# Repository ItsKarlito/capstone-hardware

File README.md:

# capstone-hardware

Capstone Software Repo: https://github.com/vincbeaulieu/Capstone_Software

BOM: https://docs.google.com/spreadsheets/d/17WK9bXRUVKC68JrJrpc6w4yRmb0iwnLNZwZWMupnYeM

Raspberry Pi Connection  

Power Supply Circuit:

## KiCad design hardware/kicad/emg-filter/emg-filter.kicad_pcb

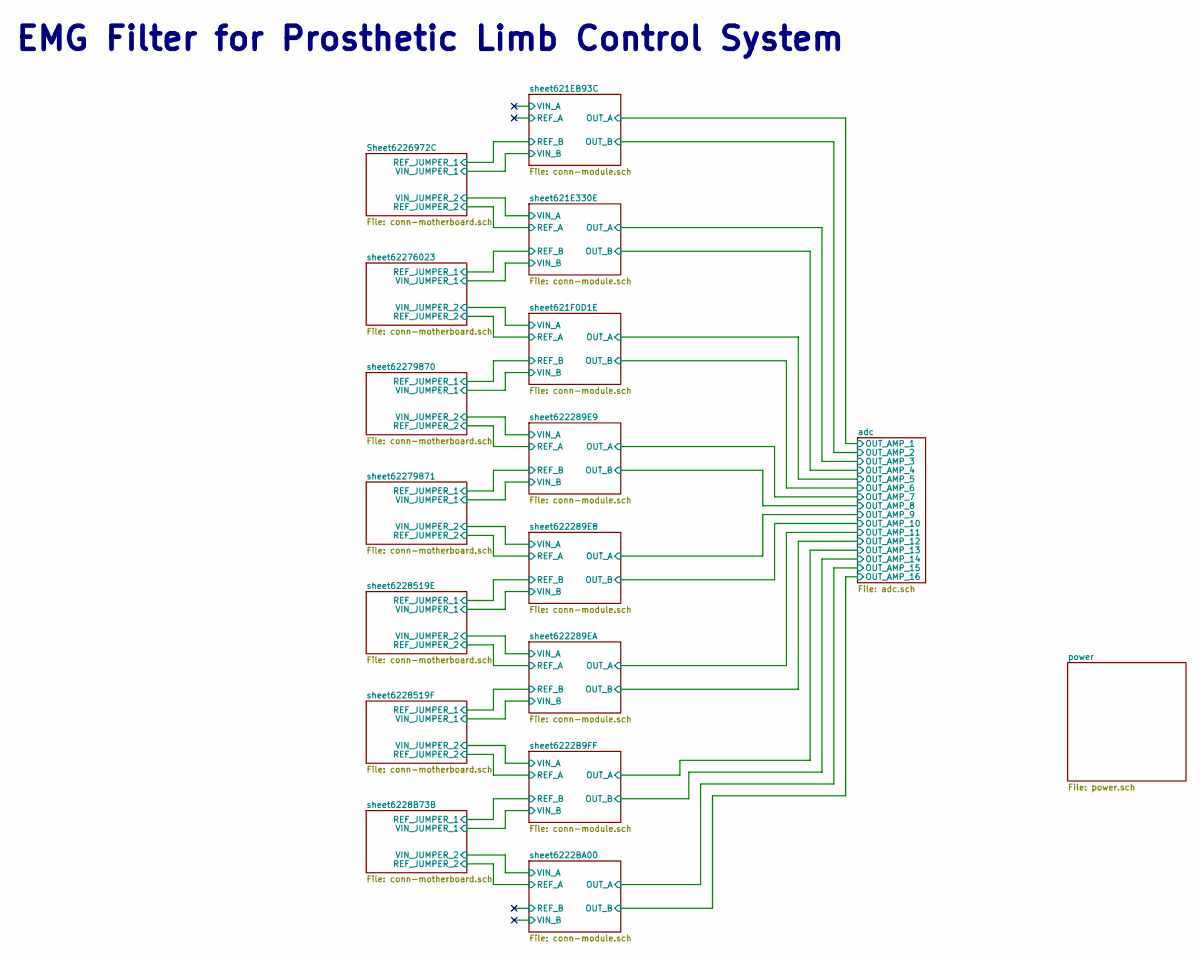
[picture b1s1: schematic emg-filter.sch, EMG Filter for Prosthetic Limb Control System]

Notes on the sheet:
EMG Filter for Prosthetic Limb Control System

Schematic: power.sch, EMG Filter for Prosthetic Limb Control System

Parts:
C1, C9: 1100uF, 50V; CP_Radial_D12.5mm_P5.00mm
C2, C10: 470uF; CP_Elec_10x10
C3, C11: 0.1uF; C_0805_2012Metric
C4, C12: 1uF; C_0805_2012Metric
C5, C13: 0.01uF; C_0805_2012Metric
C6: 0.1uF, 50V; C_0805_2012Metric
C7: 1uF, 50V; C_0805_2012Metric
C8: 0.01uF, 50V; C_0805_2012Metric
D1, D4: 1N4007; D_SOD-123F
D2, D3: LTST-C170TBKT; D_0805_2012Metric
J1: Conn_01x02; EMG_CONN_01x02
J2: Conn_01x03; CONN_01x03
R1, R6: 1k; R_0805_2012Metric
R2, R4: 1M; R_0805_2012Metric
R3, R7: 470; R_0805_2012Metric
R5: 10; R_0805_2012Metric
RV1: 10R_POT; PinHeader_1x03_P2.54mm_Vertical
U1: LM7805_TO220; TO-252-2
U2: LM7905_TO220; TO-263-2

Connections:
+5V: C2.1, C3.1, C4.1, C5.1, D1.2 (A), D2.2, R1.1, U1.3; also elsewhere on the board
+24V: C1.1, C6.1, C7.1, C8.1, D1.1 (K), J1.1, J2.1, R2.1, U1.1
-5V: C10.2, C11.2, C12.2, C13.2, D4.1 (K), R6.2, R7.2, U2.3; also elsewhere on the board
AGND: C1.2, C2.2, C3.2, C4.2, C5.2, C9.1, C10.1, C11.1, C12.1, C13.1, D3.2, J2.2, R2.2, R3.2, R4.1, R5.1, RV1.1, RV1.2; also elsewhere on the board
GNDREF: C6.2, C7.2, C8.2, C9.2, D4.2 (A), J1.2, J2.3, R4.2, U2.2
unnamed: D2.1, R3.1
unnamed: D3.1, R7.1
unnamed: R1.2, RV1.3, U1.2
unnamed: R5.2, R6.1, U2.1

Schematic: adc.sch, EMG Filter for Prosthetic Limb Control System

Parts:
C14, C16, C18, C20: 0.1uF; C_0805_2012Metric
C15, C17, C19, C21: 1.0uF; C_0805_2012Metric
J3: Conn_02x20_Odd_Even; PinHeader_2x20_P2.54mm_Vertical
U3, U4: ADC108S102; TSSOP-16_4.4x5mm_P0.65mm

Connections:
!CS_1_PI: J3.13, U3.1
!CS_2_PI: J3.15, U4.1
+3V3: C16.1, C17.1, C20.1, C21.1, J3.17, U3.13, U4.13
+5V: C14.1, C15.1, C18.1, C19.1, U3.2, U4.2; also elsewhere on the board
/adc/OUT_AMP_2: U3.5; also elsewhere on the board
/adc/OUT_AMP_4: U3.7; also elsewhere on the board
/adc/OUT_AMP_6: U3.9; also elsewhere on the board
/adc/OUT_AMP_8: U3.11; also elsewhere on the board
/adc/OUT_AMP_10: U4.5; also elsewhere on the board
/adc/OUT_AMP_12: U4.7; also elsewhere on the board
/adc/OUT_AMP_14: U4.9; also elsewhere on the board
/adc/OUT_AMP_16: U4.11; also elsewhere on the board
/sheet621E330E/OUT_A: U3.6; also elsewhere on the board
/sheet621EB93C/OUT_A: U3.4; also elsewhere on the board
/sheet621F0D1E/OUT_A: U3.8; also elsewhere on the board
/sheet6222B9FF/OUT_A: U4.8; also elsewhere on the board
/sheet6222BA00/OUT_A: U4.10; also elsewhere on the board
/sheet622289E8/OUT_A: U4.4; also elsewhere on the board
/sheet622289E9/OUT_A: U3.10; also elsewhere on the board
/sheet622289EA/OUT_A: U4.6; also elsewhere on the board
AGND: C14.2, C15.2, C16.2, C17.2, C18.2, C19.2, C20.2, C21.2, J3.25, U3.3, U3.12, U4.3, U4.12; also elsewhere on the board
DIN_MOSI_PI: J3.19, U3.14, U4.14
DOUT_MISO_PI: J3.21, U3.15, U4.15
SCLK_CLK_PI: J3.23, U3.16, U4.16

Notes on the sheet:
TX RX

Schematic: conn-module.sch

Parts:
J4, J6: Conn_01x02; PinSocket_1x02_P2.54mm_Vertical
J5: Conn_01x05; PinSocket_1x05_P2.54mm_Vertical

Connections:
+5V: J5.1; also elsewhere on the board
-5V: J5.5; also elsewhere on the board
/adc/OUT_AMP_4: J5.4; also elsewhere on the board
/sheet621E330E/OUT_A: J5.2; also elsewhere on the board
/sheet621E330E/REF_A: J4.2; also elsewhere on the board
/sheet621E330E/REF_B: J6.1; also elsewhere on the board
/sheet621E330E/VIN_A: J4.1; also elsewhere on the board
/sheet621E330E/VIN_B: J6.2; also elsewhere on the board
AGND: J5.3; also elsewhere on the board

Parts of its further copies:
J7, J9, J10, J12, J13, J15, J16, J18, J19, J21, J22, J24, J25, J27: Conn_01x02; PinSocket_1x02_P2.54mm_Vertical
J8, J11, J14, J17, J20, J23, J26: Conn_01x05; PinSocket_1x05_P2.54mm_Vertical

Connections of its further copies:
+5V: J8.1, J11.1, J14.1, J17.1, J20.1, J23.1, J26.1; also elsewhere on the board
-5V: J8.5, J11.5, J14.5, J17.5, J20.5, J23.5, J26.5; also elsewhere on the board
/adc/OUT_AMP_2: J8.4; also elsewhere on the board
/adc/OUT_AMP_6: J11.4; also elsewhere on the board
/adc/OUT_AMP_8: J17.4; also elsewhere on the board
/adc/OUT_AMP_10: J14.4; also elsewhere on the board
/adc/OUT_AMP_12: J20.4; also elsewhere on the board
/adc/OUT_AMP_14: J23.4; also elsewhere on the board
/adc/OUT_AMP_16: J26.4; also elsewhere on the board
/sheet621EB93C/OUT_A: J8.2; also elsewhere on the board
/sheet621EB93C/REF_A: J7.2
/sheet621EB93C/REF_B: J9.1; also elsewhere on the board
/sheet621EB93C/VIN_A: J7.1
/sheet621EB93C/VIN_B: J9.2; also elsewhere on the board
/sheet621F0D1E/OUT_A: J11.2; also elsewhere on the board
/sheet621F0D1E/REF_A: J10.2; also elsewhere on the board
/sheet621F0D1E/REF_B: J12.1; also elsewhere on the board
/sheet621F0D1E/VIN_A: J10.1; also elsewhere on the board
/sheet621F0D1E/VIN_B: J12.2; also elsewhere on the board
/sheet6222B9FF/OUT_A: J23.2; also elsewhere on the board
/sheet6222B9FF/REF_A: J22.2; also elsewhere on the board
/sheet6222B9FF/REF_B: J24.1; also elsewhere on the board
/sheet6222B9FF/VIN_A: J22.1; also elsewhere on the board
/sheet6222B9FF/VIN_B: J24.2; also elsewhere on the board
/sheet6222BA00/OUT_A: J26.2; also elsewhere on the board
/sheet6222BA00/REF_A: J25.2; also elsewhere on the board
/sheet6222BA00/REF_B: J27.1
/sheet6222BA00/VIN_A: J25.1; also elsewhere on the board
/sheet6222BA00/VIN_B: J27.2
/sheet622289E8/OUT_A: J14.2; also elsewhere on the board
/sheet622289E8/REF_A: J13.2; also elsewhere on the board
/sheet622289E8/REF_B: J15.1; also elsewhere on the board
/sheet622289E8/VIN_A: J13.1; also elsewhere on the board
/sheet622289E8/VIN_B: J15.2; also elsewhere on the board
/sheet622289E9/OUT_A: J17.2; also elsewhere on the board
/sheet622289E9/REF_A: J16.2; also elsewhere on the board
/sheet622289E9/REF_B: J18.1; also elsewhere on the board
/sheet622289E9/VIN_A: J16.1; also elsewhere on the board
/sheet622289E9/VIN_B: J18.2; also elsewhere on the board
/sheet622289EA/OUT_A: J20.2; also elsewhere on the board
/sheet622289EA/REF_A: J19.2; also elsewhere on the board
/sheet622289EA/REF_B: J21.1; also elsewhere on the board
/sheet622289EA/VIN_A: J19.1; also elsewhere on the board
/sheet622289EA/VIN_B: J21.2; also elsewhere on the board
AGND: J8.3, J11.3, J14.3, J17.3, J20.3, J23.3, J26.3; also elsewhere on the board

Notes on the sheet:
Female 2-pin header

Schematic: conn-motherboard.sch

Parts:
J28, J29: Conn_01x02; PinHeader_1x02_P2.54mm_Vertical

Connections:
/sheet621E330E/REF_A: J28.2; also elsewhere on the board
/sheet621E330E/VIN_A: J29.2; also elsewhere on the board
/sheet621EB93C/REF_B: J28.1; also elsewhere on the board
/sheet621EB93C/VIN_B: J29.1; also elsewhere on the board

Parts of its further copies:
J30, J31, J32, J33, J34, J35, J36, J37, J38, J39, J40, J41: Conn_01x02; PinHeader_1x02_P2.54mm_Vertical

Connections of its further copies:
/sheet621E330E/REF_B: J30.1; also elsewhere on the board
/sheet621E330E/VIN_B: J31.1; also elsewhere on the board
/sheet621F0D1E/REF_A: J30.2; also elsewhere on the board
/sheet621F0D1E/REF_B: J32.1; also elsewhere on the board
/sheet621F0D1E/VIN_A: J31.2; also elsewhere on the board
/sheet621F0D1E/VIN_B: J33.1; also elsewhere on the board
/sheet6222B9FF/REF_A: J38.2; also elsewhere on the board
/sheet6222B9FF/REF_B: J40.1; also elsewhere on the board
/sheet6222B9FF/VIN_A: J39.2; also elsewhere on the board
/sheet6222B9FF/VIN_B: J41.1; also elsewhere on the board
/sheet6222BA00/REF_A: J40.2; also elsewhere on the board
/sheet6222BA00/VIN_A: J41.2; also elsewhere on the board
/sheet622289E8/REF_A: J34.2; also elsewhere on the board
/sheet622289E8/REF_B: J36.1; also elsewhere on the board
/sheet622289E8/VIN_A: J35.2; also elsewhere on the board
/sheet622289E8/VIN_B: J37.1; also elsewhere on the board
/sheet622289E9/REF_A: J32.2; also elsewhere on the board
/sheet622289E9/REF_B: J34.1; also elsewhere on the board
/sheet622289E9/VIN_A: J33.2; also elsewhere on the board
/sheet622289E9/VIN_B: J35.1; also elsewhere on the board
/sheet622289EA/REF_A: J36.2; also elsewhere on the board
/sheet622289EA/REF_B: J38.1; also elsewhere on the board
/sheet622289EA/VIN_A: J37.2; also elsewhere on the board
/sheet622289EA/VIN_B: J39.1; also elsewhere on the board

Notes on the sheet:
Male Jumper header

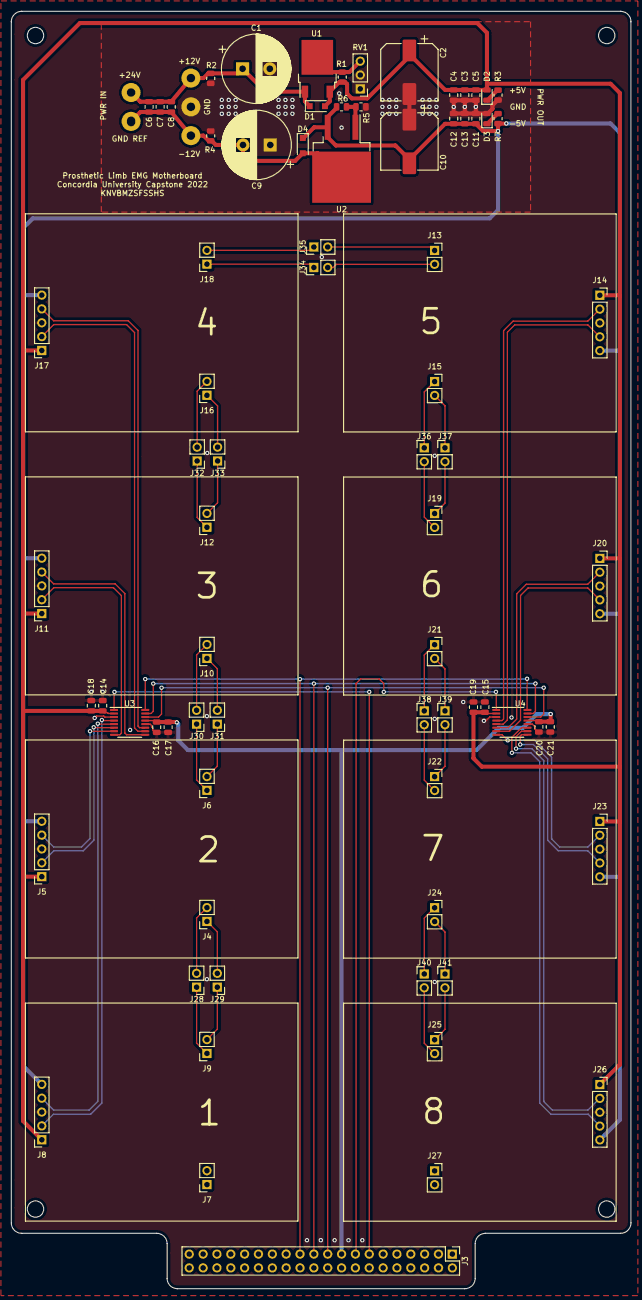
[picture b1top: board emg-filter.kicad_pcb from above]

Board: 2 copper layers, 113.7 x 234.3 mm, 78 parts (0 on the bottom side), 59 nets.

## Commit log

2021-11-11 emg amplifier project created
2021-11-11 added orcad simulation files
2021-11-16 Adding Reference Schematics for Simulation
2021-11-17 instrumental amplifier
2021-11-17 added custom emg-filter design
2021-11-17 cleaning repo
2021-11-26 added notch filter and removed precision rectifer
2021-11-26 improved notch filter quality factor
2021-12-15 added design from commit e3335dc in new page
2021-12-15 removed lck file
2021-12-15 added precision rect and notch filter
2021-12-18 added INA topology from datasheet
2021-12-19 fixed notch filter
2021-12-22 added kicad files
2021-12-22 sheet hierarchy
2021-12-22 created kicad folder
2021-12-22 added BOM link
2021-12-22 added simulation screenshots
2021-12-22 added custom opamp and adc symbols
2021-12-22 fix lib path
2021-12-22 added notch filter schematic
2021-12-22 added power flags
2021-12-22 Initial branch commit
2021-12-22 updated .gitignore
2021-12-22 removed cache file
2021-12-22 Added rectifier diagram
2021-12-23 Fix power.sch
2021-12-23 Rectifier implemented
2021-12-23 Power Supply Circuit Simulation
2021-12-23 update pin types for opamp
2021-12-23 added power connections to opamp, renamed input output labels
2021-12-23 added bandpass schematic
2021-12-23 Non-inverting amplifier (amplifier) implemented.
2021-12-23 added custom instrumental amp schematic symbol
2021-12-23 reposition supply pins for ina2332 symbol
2021-12-23 added instrumentation schematic
2021-12-23 added adc schematic
2021-12-24 Final circuit simulation
2021-12-24 gitignore
2021-12-24 16 rectifiers.
2021-12-24 16 non-inverting amplifiers
2021-12-24 Circuit Schematic
    TODO:
    - Fix GNDREF and GND annotation on all other branch/schematics to match this one.
    - Update BOM with final schematic
2021-12-26 Small fixes
2021-12-27 bandpass x16
2021-12-27 instrumentation x16
2021-12-27 notch x16
2021-12-29 screenshot update
2021-12-29 added two 1.0uF caps for VA, connected data bus together
2021-12-29 fixed incorrect SHTDWN pin connection
2021-12-29 swapped GND and GNDREF, removed connectors
2022-01-03 removed stuff on power sheet
2022-01-03 annotation
2022-01-03 linked stages by renaming labels
2022-01-03 diode and led values
2022-01-06 notes from review with Dmitry, 01-06-22
2022-01-07 removed all DS_Store
2022-01-07 sheet size and info
2022-01-07 added cap bank for op-amp supply rails, removed pi power supply
2022-01-08 added pi gnd flag
2022-01-08 Rectifier Fit on US letter format
2022-01-08 pi connector and adc
2022-01-08 Manual Merged of Rectifier Review to Main
2022-01-08 fixed rectifier
2022-01-08 Connector
2022-01-08 minor fixes
2022-01-10 fixed rect labels
2022-01-11 Added RBpi Connection Map
2022-01-11 -5V caps and cap voltages
2022-01-12 footprint association
2022-01-15 added LM4565 footprint
2022-01-15 added connector footprints
2022-01-15 slip 264k and 266k, now 2x132k and 2x133k
2022-01-15 Solving Stuff for Free
2022-01-15 Renaming Labels
2022-01-15 fixed remaining errors
2022-01-15 test commit from windows
2022-01-16 saving progress
2022-01-16 Fix Rectifier
2022-01-17 finished single channel
2022-01-20 rearranged layout
2022-01-20 restructured entire schematic to use hierarchichal labels
2022-01-20 fixed DRC errors
2022-01-20 missing footprint association
2022-01-20 saving progress, post replication
2022-01-20 Block implementation
2022-01-20 Fixed errors
2022-01-21 all channels complete
2022-01-21 compact design
2022-01-23 finished adc placement data bus routing
2022-01-23 edge cuts
2022-01-24 completed pcb
2022-01-24 added gerber files
2022-01-24 added holes for screws
2022-01-25 recalculated pours
2022-01-25 update gerber
2022-01-27 Connectors done, but annotation bad
    work will be transfer to another project
2022-01-27 saved files
2022-01-28 added 5 pin conn, got rid of filters
2022-01-28 schematic reviewed
2022-01-28 fixed label names
2022-01-28 modular design
2022-01-28 Isolating module
2022-01-29 Update pcb module
2022-01-29 Schematic Module done
    but missing 2xGND layers and +5V / -5V layers
2022-01-29 Fixed pin facing wrong side
2022-01-29 Added Layers
2022-01-29 Connected unconnected elements
2022-01-29 fixed length
2022-01-30 Amplifier done
2022-01-30 Done - Ready for manufacturing
2022-01-30 Done
2022-01-30 aligning pins to fit on motherboard
2022-01-30 fixed shematic
2022-01-30 text layer and footprint
2022-02-03 added model number
2022-02-03 gerbers
2022-02-03 gerber zip
2022-02-03 gerber update
2022-02-03 Updated diode footprint
    and changed 5k to 4.99k resistor
    reason: 4.99k resistor are less expensive and won't affect the output of the design
2022-02-03 Update wiring
2022-02-03 changed local lib path
2022-02-13 half of channels placed
2022-02-14 channels placed
2022-02-14 analog to adc traced
2022-02-15 reference placement
2022-02-17 converted to 2 layers
2022-02-18 pcb mounting holes
2022-02-18 fixed power rails thickness
